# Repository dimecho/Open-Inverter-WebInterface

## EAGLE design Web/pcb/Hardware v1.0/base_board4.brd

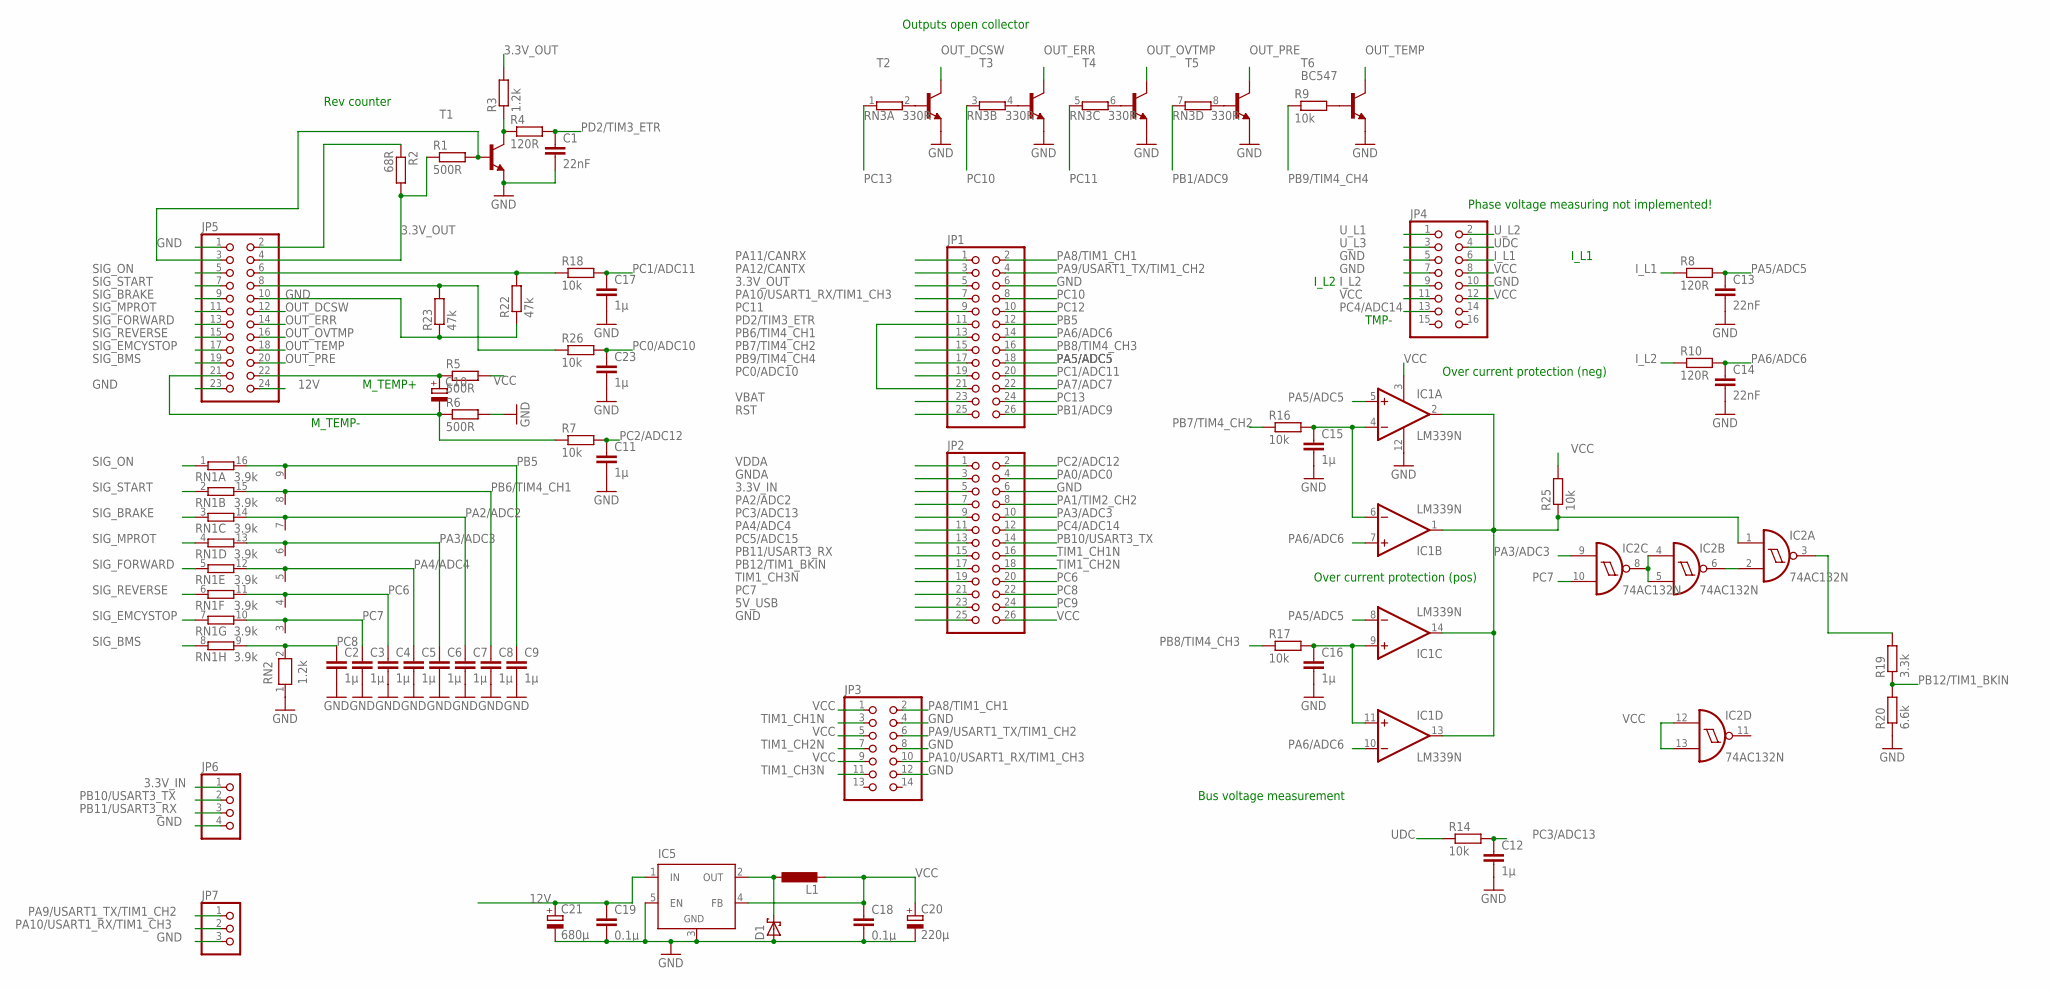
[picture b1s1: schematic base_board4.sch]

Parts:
C1, C13, C14: 22nF; C025-024X044
C2, C3, C4, C5, C6, C7, C8, C9, C11, C12, C15, C16, C17, C23: 1µ; C025-024X044
C10: CPOL-EUE2-4; E2-4
C18, C19: 0.1µ; C050-024X044
C20: 220µ; E2-4
C21: 680µ; E2,5-5
D1: SCHOTTKY-DIODEDO201T15; DO201T15
IC1: LM339N; DIL14
IC2: 74AC132N; DIL14
IC5: LM2596TV; TO220-51
JP1, JP2: PINHD-2X13; 2X13
JP3: PINHD-2X7; 2X07
JP4: PINHD-2X8; 2X08
JP5: PINHD-2X12; 2X12
JP6: PINHD-1X4; 1X04
JP7: PINHD-1X3; 1X03
L1: L-EUTJ3-U1; TJ3-U1
R1, R5, R6: 500R; 0207/10
R2: 68R; 0207/10
R3: 1.2k; 0207/10
R4, R8, R10: 120R; 0207/10
R7, R9, R14, R16, R17, R18, R25, R26: 10k; 0207/10
R19: 3.3k; 0207/10
R20: 6.6k; 0207/10
R22, R23: 47k; 0207/10
RN1: 3.9k; DIL16
RN2: 1.2k; RN-9
RN3: 330R; SIL8
T1: BC547B-NPN-TO92-EBC; TO92-EBC
T2, T3, T4, T5: -NPN-TO92-EBC; TO92-EBC
T6: BC547; TO92

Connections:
3.3V_IN: JP2.5, JP6.1
3.3V_OUT: JP1.5, JP5.4, R1.1, R2.2, R3.2
5V_USB: JP2.23
12V: C19.1, C21.+, IC5.1 (IN), JP5.24
GND: C1.2, C2.2, C3.2, C4.2, C5.2, C6.2, C7.2, C8.2, C9.2, C11.2, C12.2, C13.2, C14.2, C15.2, C16.2, C17.2, C18.2, C19.2, C20.-, C21.-, C23.2, D1.A, IC1.12 (GND), IC2.7 (GND), IC5.3 (GND), IC5.5 (EN), JP1.6, JP2.6, JP2.25, JP3.4, JP3.8, JP3.12, JP4.5, JP4.7, JP4.10, JP5.1, JP5.10, JP5.23, JP6.4, JP7.3, R6.2, R20.1, R22.1, R23.1, RN2.1, T1.E, T2.E, T3.E, T4.E, T5.E, T6.1 (E)
GNDA: JP2.3
I_L1: JP4.6, R8.1
I_L2: JP4.9, R10.1
N2: R3.1, R4.1, T1.C
unnamed: RN3.2, T2.B
unnamed: RN3.4 (2), T3.B
unnamed: JP5.2, R2.1
unnamed: RN3.6 (2), T4.B
unnamed: JP5.3, R1.2, T1.B
unnamed: RN3.8 (2), T5.B
unnamed: R9.2, T6.2 (B)
unnamed: IC2.3 (O), R19.2
unnamed: C16.1, IC1.9 (+IN), IC1.11 (+IN), R17.2
unnamed: IC2.2 (I1), IC2.6 (O)
unnamed: C10.+, JP5.22, R5.1
unnamed: D1.C, IC5.2 (OUT), L1.1
unnamed: C15.1, IC1.4 (-IN), IC1.6 (-IN), R16.2
unnamed: C10.-, JP5.21, R6.1, R7.1
unnamed: IC2.4 (I0), IC2.5 (I1), IC2.8 (O)
unnamed: IC1.1 (OUT), IC1.2 (OUT), IC1.13 (OUT), IC1.14 (OUT), IC2.1 (I0), R25.1
OUT_DCSW: JP5.12, T2.C
OUT_ERR: JP5.14, T3.C
OUT_OVTMP: JP5.16, T4.C
OUT_PRE: JP5.20, T5.C
OUT_TEMP: JP5.18, T6.3 (C)
PA0/ADC0: JP2.4
PA1/TIM2_CH2: JP2.8
PA2/ADC2: C7.1, JP2.7, RN1.14 (2), RN2.7
PA3/ADC3: C6.1, IC2.9 (I0), JP2.10, RN1.13 (2), RN2.6
PA4/ADC4: C5.1, JP2.11, RN1.12 (2), RN2.5
PA5/ADC5: C13.1, IC1.5 (+IN), IC1.8 (-IN), JP1.18, R8.2
PA6/ADC6: C14.1, IC1.7 (+IN), IC1.10 (-IN), JP1.14, R10.2
PA7/ADC7: JP1.22
PA8/TIM1_CH1: JP1.2, JP3.2
PA9/USART1_TX/TIM1_CH2: JP1.4, JP3.6, JP7.1
PA10/USART1_RX/TIM1_CH3: JP1.7, JP3.10, JP7.2
PA11/CANRX: JP1.1
PA12/CANTX: JP1.3
PB1/ADC9: JP1.26, RN3.7 (1)
PB5: C9.1, JP1.12, RN1.16 (2), RN2.9
PB6/TIM4_CH1: C8.1, JP1.13, RN1.15 (2), RN2.8
PB7/TIM4_CH2: JP1.15, R16.1
PB8/TIM4_CH3: JP1.16, R17.1
PB9/TIM4_CH4: JP1.17, R9.1
PB10/USART3_TX: JP2.14, JP6.2
PB11/USART3_RX: JP2.15, JP6.3
PB12/TIM1_BKIN: JP2.17, R19.1, R20.2
PC0/ADC10: C23.1, JP1.19, R26.2
PC1/ADC11: C17.1, JP1.20, R18.2
PC2/ADC12: C11.1, JP2.2, R7.2
PC3/ADC13: C12.1, JP2.9, R14.2
PC4/ADC14: JP2.12, JP4.13
PC5/ADC15: JP2.13
PC6: C4.1, JP2.20, RN1.11 (2), RN2.4
PC7: C3.1, IC2.10 (I1), JP2.21, RN1.10 (2), RN2.3
PC8: C2.1, JP2.22, RN1.9 (2), RN2.2
PC9: JP2.24
PC10: JP1.8, RN3.3 (1)
PC11: JP1.9, RN3.5 (1)
PC12: JP1.10
PC13: JP1.24, RN3.1
PD2/TIM3_ETR: C1.1, JP1.11, JP1.21, R4.2
RST: JP1.25
SIG_BMS: JP5.19, RN1.8 (1)
SIG_BRAKE: JP5.9, RN1.3 (1)
SIG_EMCYSTOP: JP5.17, RN1.7 (1)
SIG_FORWARD: JP5.13, RN1.5 (1)
SIG_MPROT: JP5.11, RN1.4 (1)
SIG_ON: JP5.5, RN1.1
SIG_REVERSE: JP5.15, RN1.6 (1)
SIG_START: JP5.7, RN1.2 (1)
TIM1_CH1N: JP2.16, JP3.3
TIM1_CH2N: JP2.18, JP3.7
TIM1_CH3N: JP2.19, JP3.11
UDC: JP4.4, R14.1
U_L1: JP4.1
U_L2: JP4.2
U_L3: JP4.3
VBAT: JP1.23
VCC: C18.1, C20.+, IC1.3 (V+), IC2.12 (I0), IC2.13 (I1), IC2.14 (VCC), IC5.4 (FB), JP2.26, JP3.1, JP3.5, JP3.9, JP4.8, JP4.11, JP4.12, L1.2, R5.2, R25.2
VDDA: JP2.1
X: JP5.6, R18.1, R22.2
Y: JP5.8, R23.2, R26.1

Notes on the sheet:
M_TEMP+
M_TEMP-
TMP-
Over current protection (pos)
Outputs open collector
Phase voltage measuring not implemented!
Bus voltage measurement
Rev counter
Over current protection (neg)
I_L1
I_L2

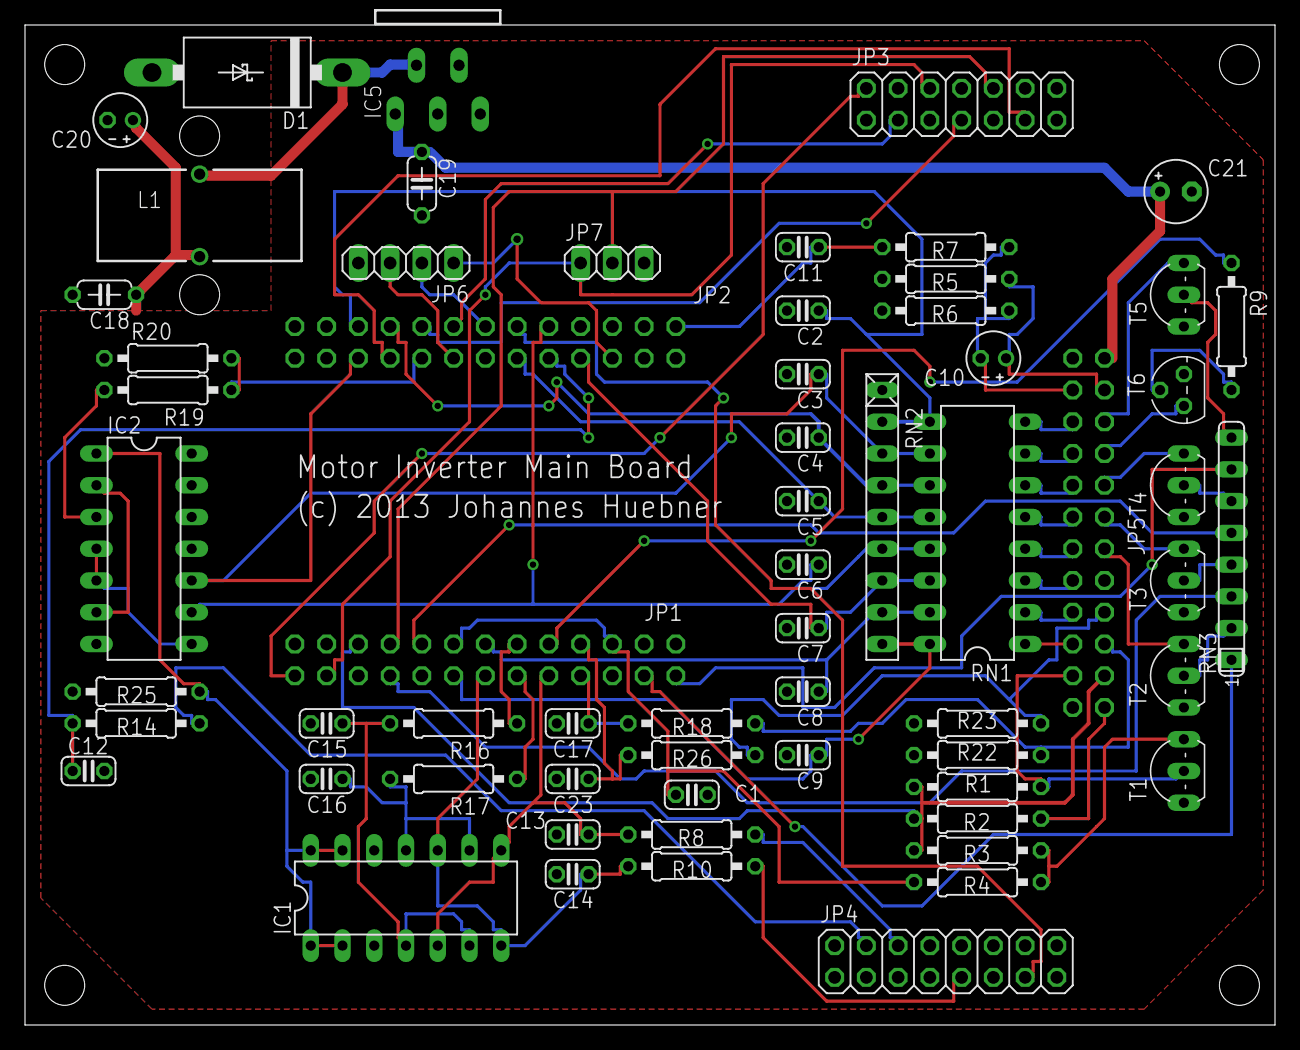
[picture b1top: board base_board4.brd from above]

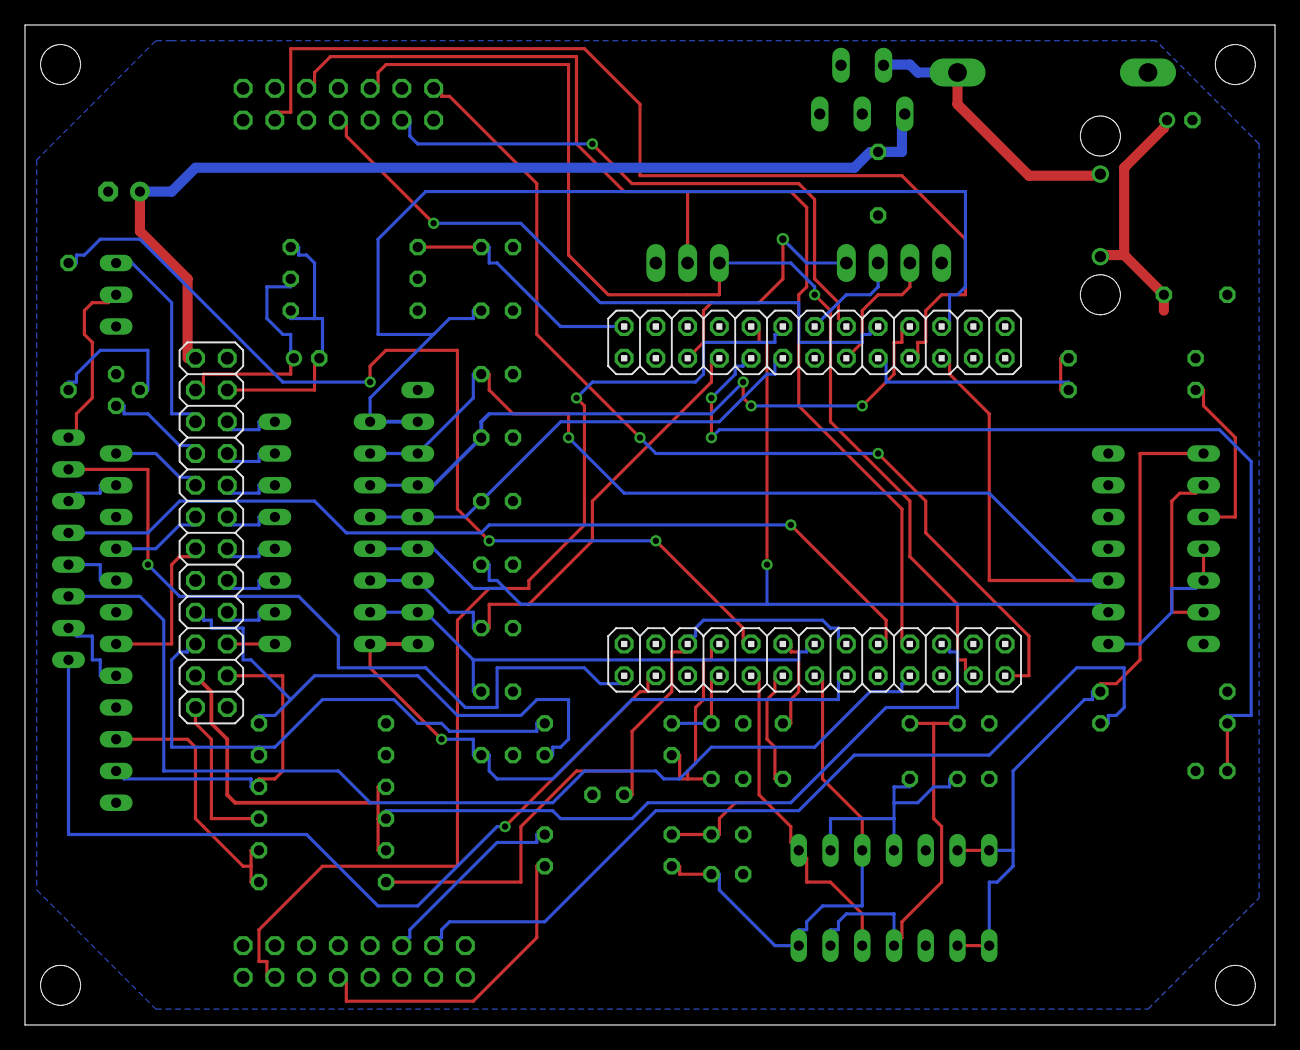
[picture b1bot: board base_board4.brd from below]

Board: 2 copper layers, 100.0 x 80.0 mm, 63 parts (3 on the bottom side), 72 nets.

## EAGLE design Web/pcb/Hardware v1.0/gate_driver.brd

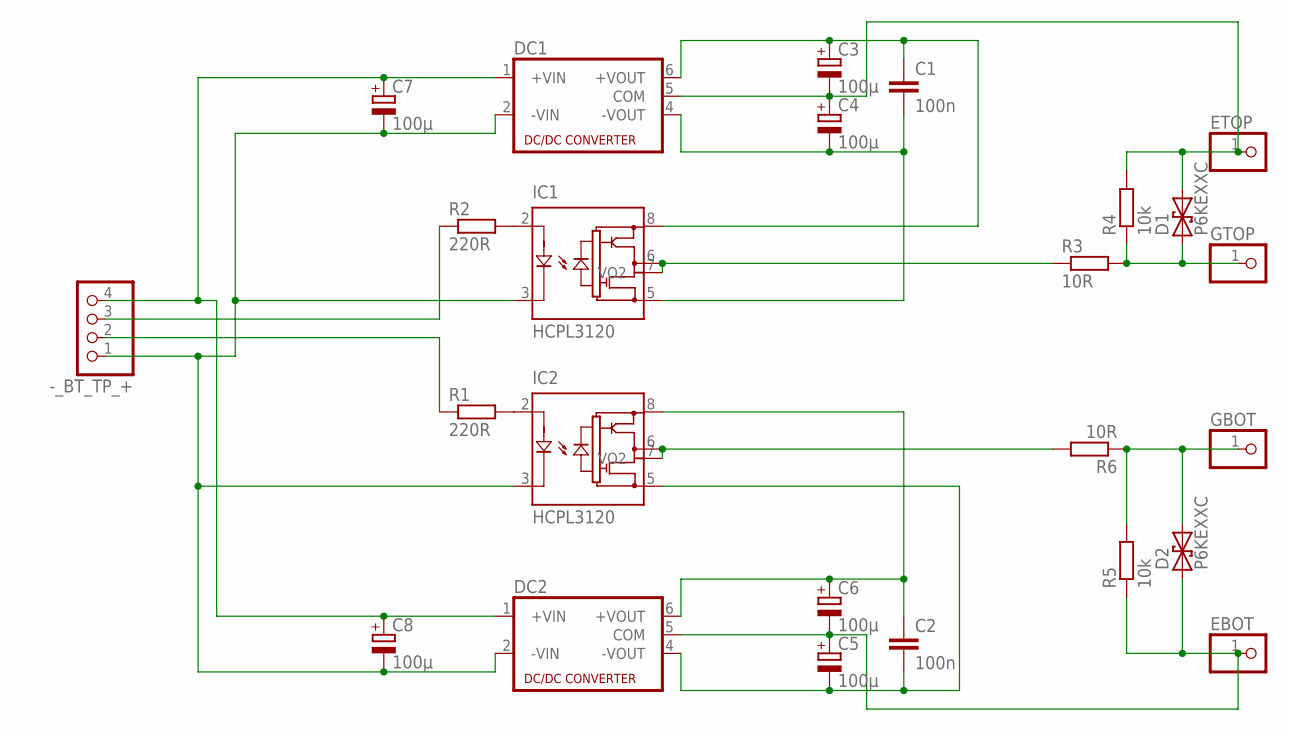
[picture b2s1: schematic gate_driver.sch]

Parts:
-_BT_TP_+: PINHD-1X4; 1X04
C1, C2: 100n; C050-025X075
C3, C4, C5, C6: 100µ; E2,5-6E
C7, C8: 100µ; E2,5-5
D1, D2: P6KEXXC; CB417-15
DC1, DC2: NMA
EBOT: PINHD-1X1; 1X01
ETOP: PINHD-1X1; 1X01
GBOT: PINHD-1X1; 1X01
GTOP: PINHD-1X1; 1X01
IC1, IC2: HCPL3120; DIL08
R1, R2: 220R; 0207/10
R3, R6: 10R; 0309/12
R4, R5: 10k; 0207/10

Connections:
EBOT: C5.+, C6.-, D2.A (1), DC2.5 (COM), EBOT.1, R5.1
ETOP: C3.-, C4.+, D1.C (2), DC1.5 (COM), ETOP.1, R4.2
GBOT: D2.C (2), GBOT.1, R5.2, R6.1
GND: -_BT_TP_+.1, C7.-, C8.-, DC1.2 (-VIN), DC2.2 (-VIN), IC1.3 (CATHODE), IC2.3 (CATHODE)
GTOP: D1.A (1), GTOP.1, R3.2, R4.1
unnamed: IC2.2 (ANODE), R1.2
unnamed: IC1.2 (ANODE), R2.2
unnamed: C1.2, C4.-, DC1.4 (-VOUT), IC1.5 (VEE)
unnamed: C1.1, C3.+, DC1.6 (+VOUT), IC1.8 (VCC)
unnamed: C2.1, C6.+, DC2.6 (+VOUT), IC2.8 (VCC)
unnamed: C2.2, C5.-, DC2.4 (-VOUT), IC2.5 (VEE)
unnamed: IC1.6 (VO), IC1.7 (VO2), R3.1
unnamed: IC2.6 (VO), IC2.7 (VO2), R6.2
unnamed: -_BT_TP_+.4, C7.+, C8.+, DC1.1 (+VIN), DC2.1 (+VIN)
unnamed: -_BT_TP_+.3, R2.1
unnamed: -_BT_TP_+.2, R1.1

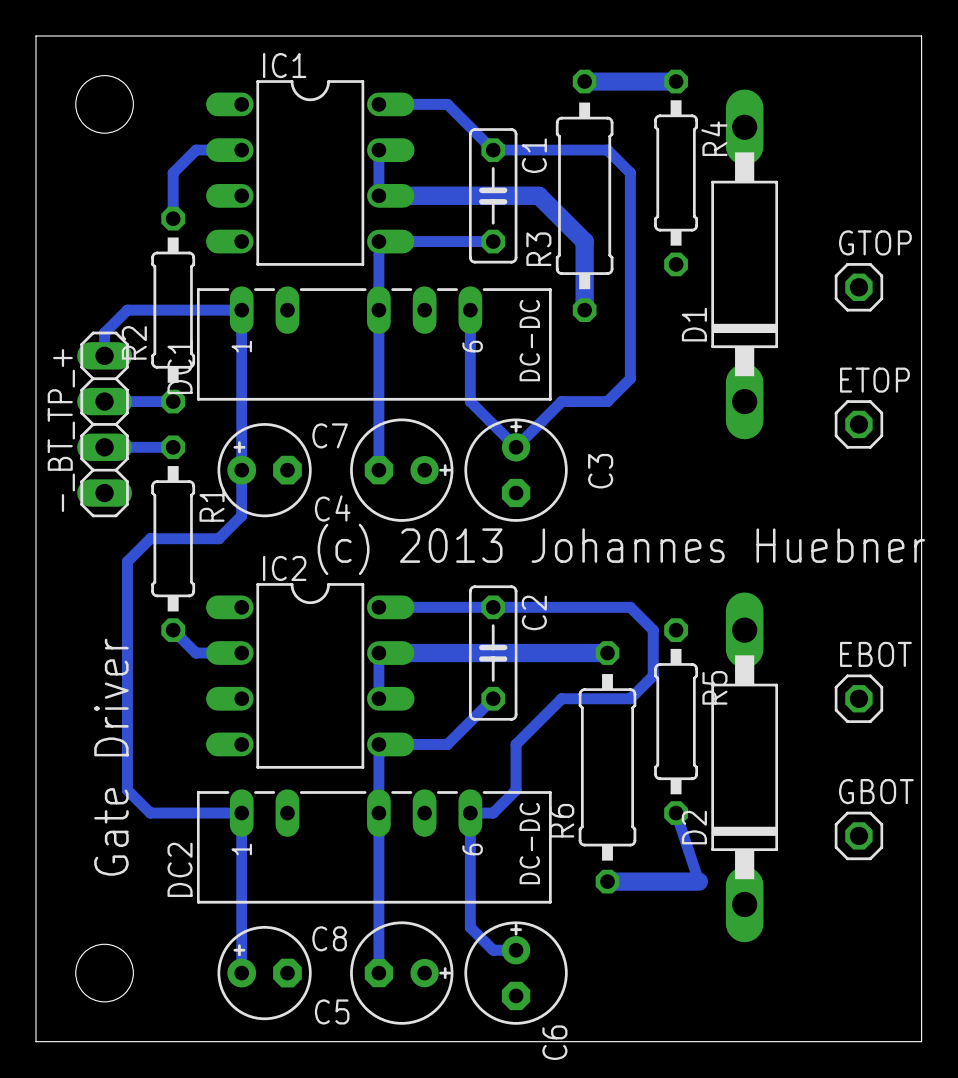
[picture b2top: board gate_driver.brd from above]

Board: 2 copper layers, 49.2 x 55.9 mm, 25 parts (0 on the bottom side), 16 nets.

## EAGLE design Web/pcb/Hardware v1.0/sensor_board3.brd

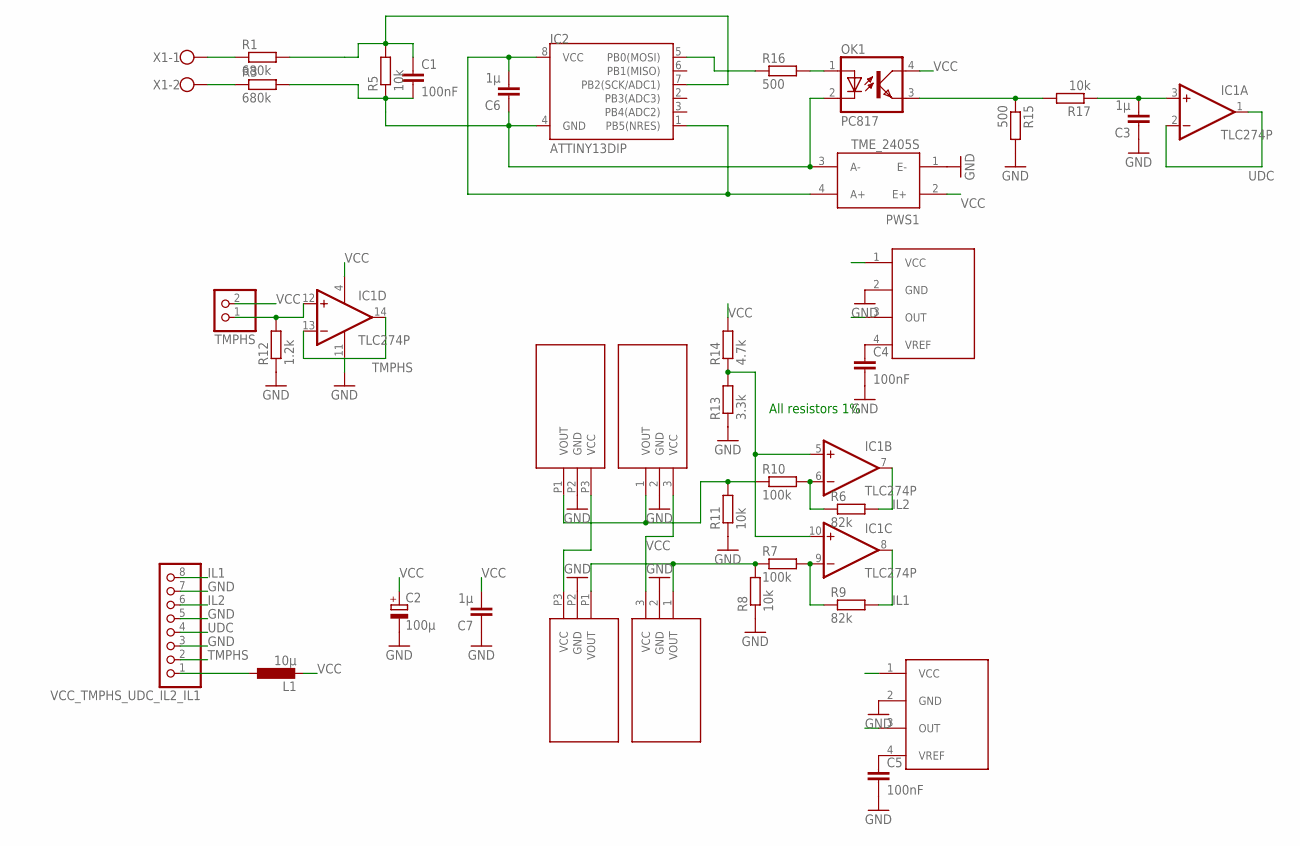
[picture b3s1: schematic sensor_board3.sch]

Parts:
C1, C4, C5: 100nF; C025-024X044
C2: 100µ; E2,5-6E
C3, C6, C7: 1µ; C025-024X044
IC1: TLC274P; DIL14
IC2: ATTINY13DIP; DIP08
L1: 10µ; 0207/12
OK1: PC817; DIL04
PWS1: TME_2405S; TMEXXXXS
R1, R3: 680k; 0207/10
R5, R8, R11, R17: 10k; 0207/10
R6, R9: 82k; 0207/10
R7, R10: 100k; 0207/10
R12: 1.2k; 0207/10
R13: 3.3k; 0207/10
R14: 4.7k; 0207/10
R15, R16: 500; 0207/10
TMPHS: PINHD-1X2; 1X02
U$1, U$2: TAMURA_L01Z_S05
U$3, U$4: HTFS
U$5, U$6: TAMURA_L06P_S05L06P; TAMURA_L06P_S05
VCC_TMPHS_UDC_IL2_IL1: PINHD-1X8; 1X08
X1: W237-102

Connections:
GND: C2.-, C3.1, C4.2, C5.2, C7.1, IC1.11 (V-), PWS1.1 (E-), R8.1, R11.1, R12.1, R13.1, R15.2, U$1.2 (GND), U$2.2 (GND), U$3.2 (GND), U$4.2 (GND), U$5.P2 (GND), U$6.P2 (GND), VCC_TMPHS_UDC_IL2_IL1.3, VCC_TMPHS_UDC_IL2_IL1.5, VCC_TMPHS_UDC_IL2_IL1.7
GND2: C1.2, C6.1, IC2.4 (GND), OK1.2 (C), PWS1.3 (A-), R3.2, R5.1
IL1: IC1.8 (OUT), R9.2, VCC_TMPHS_UDC_IL2_IL1.8
IL2: IC1.7 (OUT), R6.2, VCC_TMPHS_UDC_IL2_IL1.6
unnamed: IC1.5 (+IN), IC1.10 (+IN), R13.2, R14.1
unnamed: C1.1, IC2.7 (PB2(SCK/ADC1)), R1.2, R5.2
unnamed: R1.1, X1.1
unnamed: R3.1, X1.2
unnamed: L1.1, VCC_TMPHS_UDC_IL2_IL1.1
unnamed: IC1.9 (-IN), R7.2, R9.1
unnamed: IC1.6 (-IN), R6.1, R10.2
unnamed: OK1.3 (EMIT), R15.1, R17.2
unnamed: C4.1, U$3.4 (VREF)
unnamed: C5.1, U$4.4 (VREF)
unnamed: IC1.12 (+IN), R12.2, TMPHS.1
unnamed: OK1.1 (A), R16.2
unnamed: IC2.5 (PB0(MOSI)), R16.1
unnamed: C3.2, IC1.3 (+IN), R17.1
TMPHS: IC1.13 (-IN), IC1.14 (OUT), VCC_TMPHS_UDC_IL2_IL1.2
UDC: IC1.1 (OUT), IC1.2 (-IN), VCC_TMPHS_UDC_IL2_IL1.4
VCC: C2.+, C7.2, IC1.4 (V+), L1.2, OK1.4 (COL), PWS1.2 (E+), R14.2, TMPHS.2, U$1.3 (VCC), U$2.3 (VCC), U$3.1 (VCC), U$4.1 (VCC), U$5.P3 (VCC), U$6.P3 (VCC)
VCC2: C6.2, IC2.1 (PB5(NRES)), IC2.8 (VCC), PWS1.4 (A+)
VOUT1: R7.1, R8.2, U$2.1 (VOUT), U$4.3 (OUT), U$6.P1 (VOUT)
VOUT2: R10.1, R11.2, U$1.1 (VOUT), U$3.3 (OUT), U$5.P1 (VOUT)

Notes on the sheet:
All resistors 1%

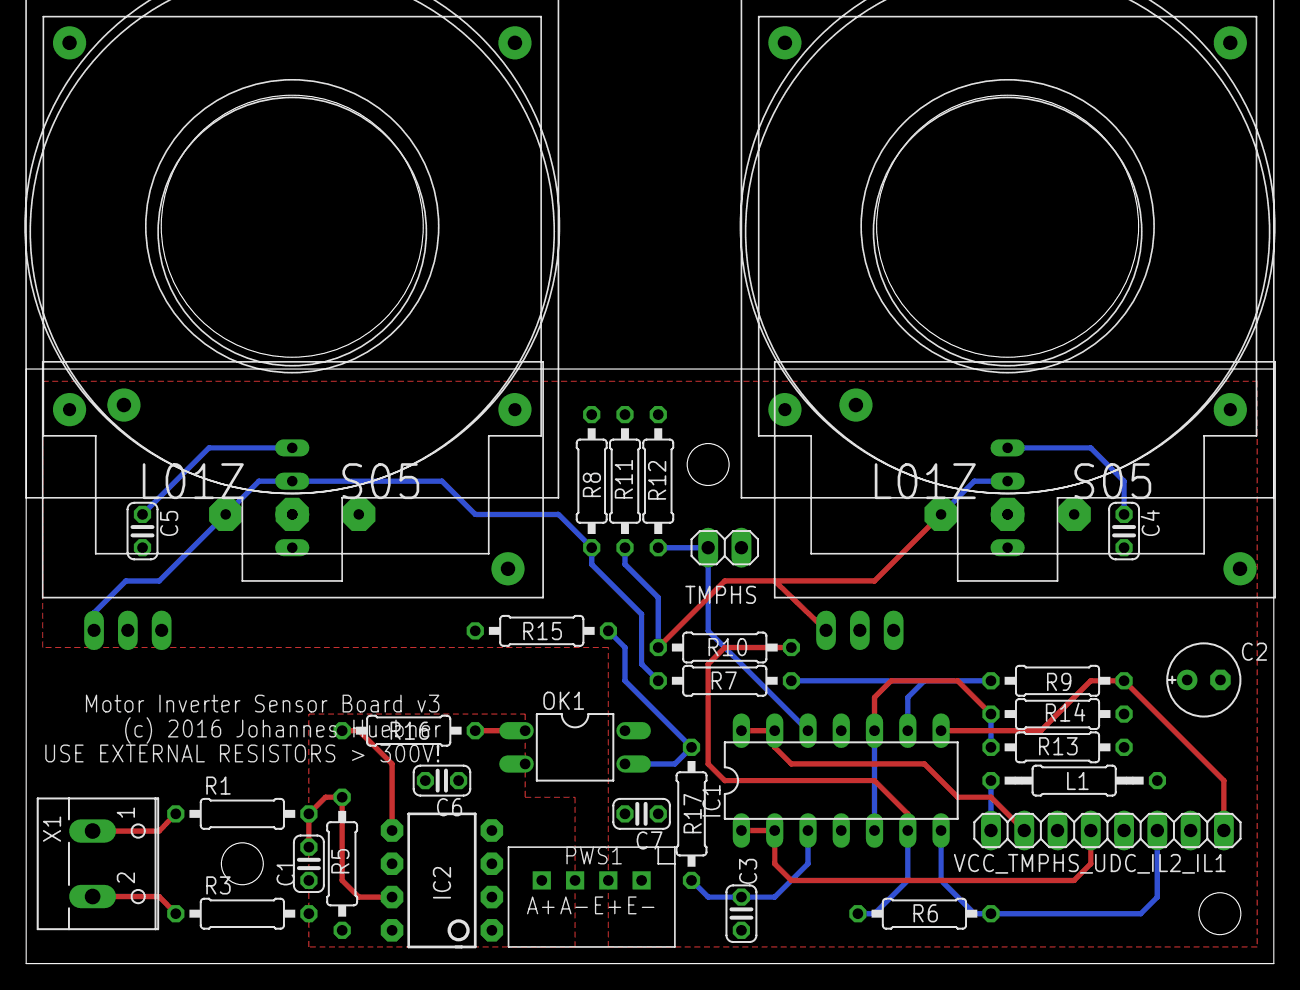
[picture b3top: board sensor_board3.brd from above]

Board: 2 copper layers, 95.2 x 45.4 mm, 36 parts (0 on the bottom side), 24 nets.

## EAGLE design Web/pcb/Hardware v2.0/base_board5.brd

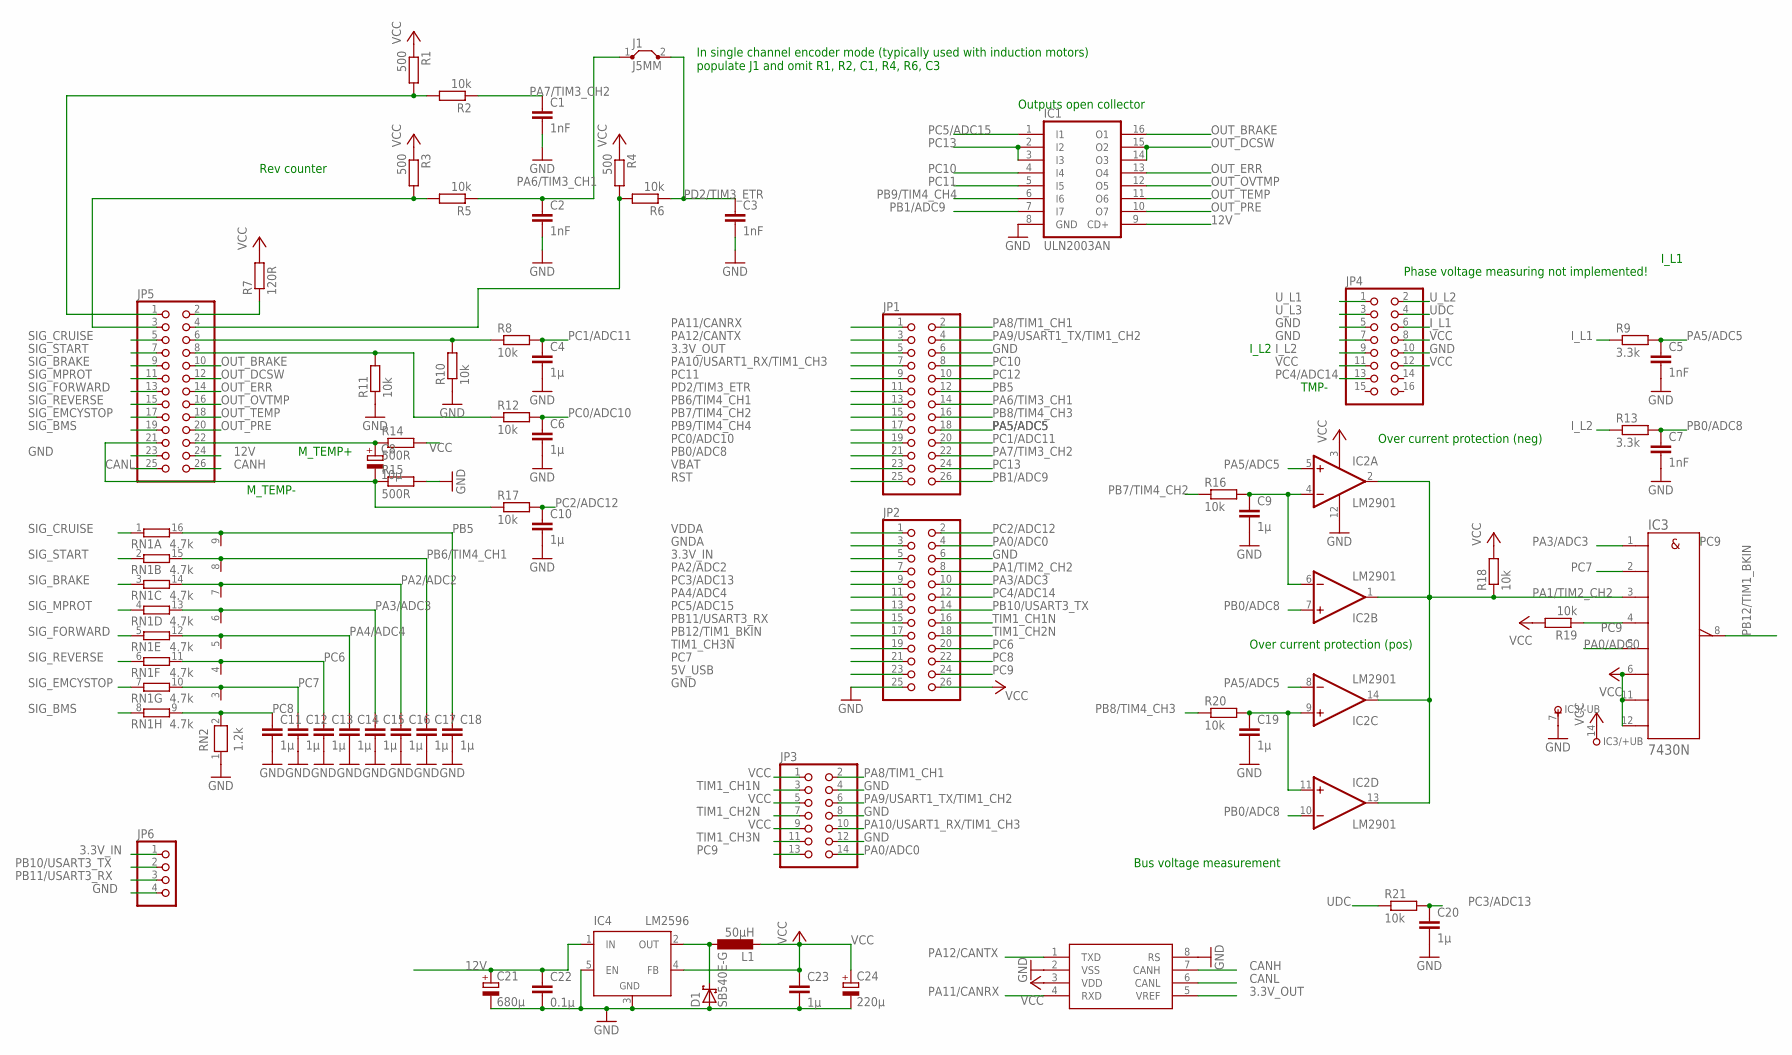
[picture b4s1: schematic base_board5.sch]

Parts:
C1, C2, C3, C5, C7: 1nF; C025-024X044
C4, C6, C9, C10, C11, C12, C13, C14, C15, C16, C17, C18, C19, C20, C23: 1µ; C025-024X044
C8: 10µ; E2-4
C21: 680µ; E2,5-5
C22: 0.1µ; C050-024X044
C24: 220µ; E2-4
D1: SB540E-G; DO201T15
IC1: ULN2003AN; DIL16
IC2: LM2901; DIL14
IC3: 7430N; DIL14
IC4: LM2596; TO220-51
IC5: MCP2562P; DIL08
J1: J5MM; 05
JP1, JP2, JP5: PINHD-2X13; 2X13
JP3: PINHD-2X7; 2X07
JP4: PINHD-2X8; 2X08
JP6: PINHD-1X4; 1X04
L1: 50µH; TJ3-U1
R1, R3, R4: 500; 0207/10
R2, R5, R6, R8, R10, R11, R12, R16, R17, R18, R19, R20, R21: 10k; 0207/10
R7: 120R; 0207/10
R9, R13: 3.3k; 0207/10
R14, R15: 500R; 0207/10
RN1: 4.7k; DIL16
RN2: 1.2k; RN-9

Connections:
3.3V_IN: JP2.5, JP6.1
3.3V_OUT: IC5.5 (VREF), JP1.5
5V_USB: JP2.23
12V: C21.+, C22.1, IC1.9 (CD+), IC4.1 (IN), JP5.24
CANH: IC5.7 (CANH), JP5.26
CANL: IC5.6 (CANL), JP5.25
GND: C1.2, C2.2, C3.2, C4.2, C5.2, C6.2, C7.2, C9.2, C10.2, C11.2, C12.2, C13.2, C14.2, C15.2, C16.2, C17.2, C18.2, C19.2, C20.2, C21.-, C22.2, C23.2, C24.-, D1.A, IC1.8 (GND), IC2.12 (GND), IC3.7 (-UB), IC4.3 (GND), IC4.5 (EN), IC5.2 (VSS), IC5.8 (RS), JP1.6, JP2.6, JP2.25, JP3.4, JP3.8, JP3.12, JP4.5, JP4.7, JP4.10, JP5.23, JP6.4, R10.1, R11.1, R15.2, RN2.1
GNDA: JP2.3
I_L1: JP4.6, R9.1
I_L2: JP4.9, R13.1
unnamed: JP5.2, R7.1
unnamed: JP5.3, R3.2, R5.2
unnamed: JP5.1, R1.2, R2.2
unnamed: C19.1, IC2.9 (+IN), IC2.11 (+IN), R20.2
unnamed: JP5.4, R4.2, R6.2
unnamed: C8.+, JP5.22, R14.1
unnamed: D1.C, IC4.2 (OUT), L1.1
unnamed: C9.1, IC2.4 (-IN), IC2.6 (-IN), R16.2
unnamed: C8.-, JP5.21, R15.1, R17.1
OUT_BRAKE: IC1.16 (O1), JP5.10
OUT_DCSW: IC1.14 (O3), IC1.15 (O2), JP5.12
OUT_ERR: IC1.13 (O4), JP5.14
OUT_OVTMP: IC1.12 (O5), JP5.16
OUT_PRE: IC1.10 (O7), JP5.20
OUT_TEMP: IC1.11 (O6), JP5.18
PA0/ADC0: IC3.5 (E), JP2.4, JP3.14
PA1/TIM2_CH2: IC2.1 (OUT), IC2.2 (OUT), IC2.13 (OUT), IC2.14 (OUT), IC3.3 (C), JP2.8, R18.1
PA2/ADC2: C16.1, JP2.7, RN1.14 (2), RN2.7
PA3/ADC3: C15.1, IC3.1 (A), JP2.10, RN1.13 (2), RN2.6
PA4/ADC4: C14.1, JP2.11, RN1.12 (2), RN2.5
PA5/ADC5: C5.1, IC2.5 (+IN), IC2.8 (-IN), JP1.18, R9.2
PA6/TIM3_CH1: C2.1, J1.1, JP1.14, R5.1
PA7/TIM3_CH2: C1.1, JP1.22, R2.1
PA8/TIM1_CH1: JP1.2, JP3.2
PA9/USART1_TX/TIM1_CH2: JP1.4, JP3.6
PA10/USART1_RX/TIM1_CH3: JP1.7, JP3.10
PA11/CANRX: IC5.4 (RXD), JP1.1
PA12/CANTX: IC5.1 (TXD), JP1.3
PB0/ADC8: C7.1, IC2.7 (+IN), IC2.10 (-IN), JP1.21, R13.2
PB1/ADC9: IC1.7 (I7), JP1.26
PB5: C18.1, JP1.12, RN1.16 (2), RN2.9
PB6/TIM4_CH1: C17.1, JP1.13, RN1.15 (2), RN2.8
PB7/TIM4_CH2: JP1.15, R16.1
PB8/TIM4_CH3: JP1.16, R20.1
PB9/TIM4_CH4: IC1.6 (I6), JP1.17
PB10/USART3_TX: JP2.14, JP6.2
PB11/USART3_RX: JP2.15, JP6.3
PB12/TIM1_BKIN: IC3.8 (Y), JP2.17
PC0/ADC10: C6.1, JP1.19, R12.2
PC1/ADC11: C4.1, JP1.20, R8.2
PC2/ADC12: C10.1, JP2.2, R17.2
PC3/ADC13: C20.1, JP2.9, R21.2
PC4/ADC14: JP2.12, JP4.13
PC5/ADC15: IC1.1 (I1), JP2.13
PC6: C13.1, JP2.20, RN1.11 (2), RN2.4
PC7: C12.1, IC3.2 (B), JP2.21, RN1.10 (2), RN2.3
PC8: C11.1, JP2.22, RN1.9 (2), RN2.2
PC9: IC3.4 (D), JP2.24, JP3.13, R19.1
PC10: IC1.4 (I4), JP1.8
PC11: IC1.5 (I5), JP1.9
PC12: JP1.10
PC13: IC1.2 (I2), IC1.3 (I3), JP1.24
PD2/TIM3_ETR: C3.1, J1.2, JP1.11, R6.1
RST: JP1.25
SIG_BMS: JP5.19, RN1.8 (1)
SIG_BRAKE: JP5.9, RN1.3 (1)
SIG_CRUISE: JP5.5, RN1.1
SIG_EMCYSTOP: JP5.17, RN1.7 (1)
SIG_FORWARD: JP5.13, RN1.5 (1)
SIG_MPROT: JP5.11, RN1.4 (1)
SIG_REVERSE: JP5.15, RN1.6 (1)
SIG_START: JP5.7, RN1.2 (1)
TIM1_CH1N: JP2.16, JP3.3
TIM1_CH2N: JP2.18, JP3.7
TIM1_CH3N: JP2.19, JP3.11
UDC: JP4.4, R21.1
U_L1: JP4.1
U_L2: JP4.2
U_L3: JP4.3
VBAT: JP1.23
VCC: C23.1, C24.+, IC2.3 (V+), IC3.6 (F), IC3.11 (G), IC3.12 (H), IC3.14 (+UB), IC4.4 (FB), IC5.3 (VDD), JP2.26, JP3.1, JP3.5, JP3.9, JP4.8, JP4.11, JP4.12, L1.2, R1.1, R3.1, R4.1, R7.2, R14.2, R18.2, R19.2
VDDA: JP2.1
X: JP5.6, R8.1, R10.2
Y: JP5.8, R11.2, R12.1

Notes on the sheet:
M_TEMP+
M_TEMP-
TMP-
Over current protection (pos)
Outputs open collector
Phase voltage measuring not implemented!
Bus voltage measurement
Rev counter
Over current protection (neg)
I_L1
I_L2
In single channel encoder mode (typically used with induction motors) populate J1 and omit R1, R2, C1, R4, R6, C3

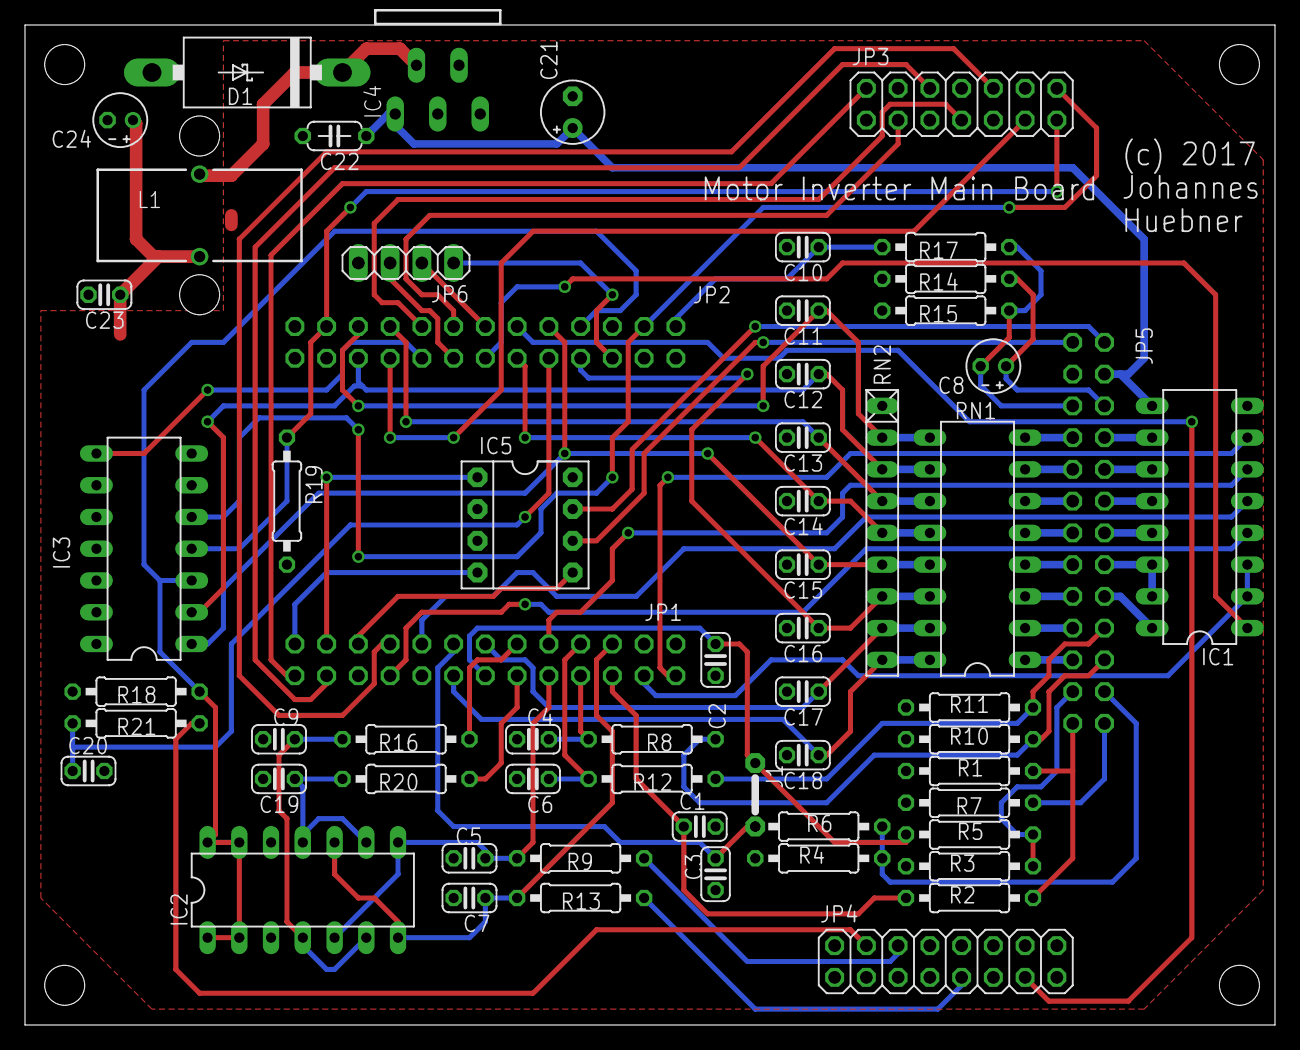
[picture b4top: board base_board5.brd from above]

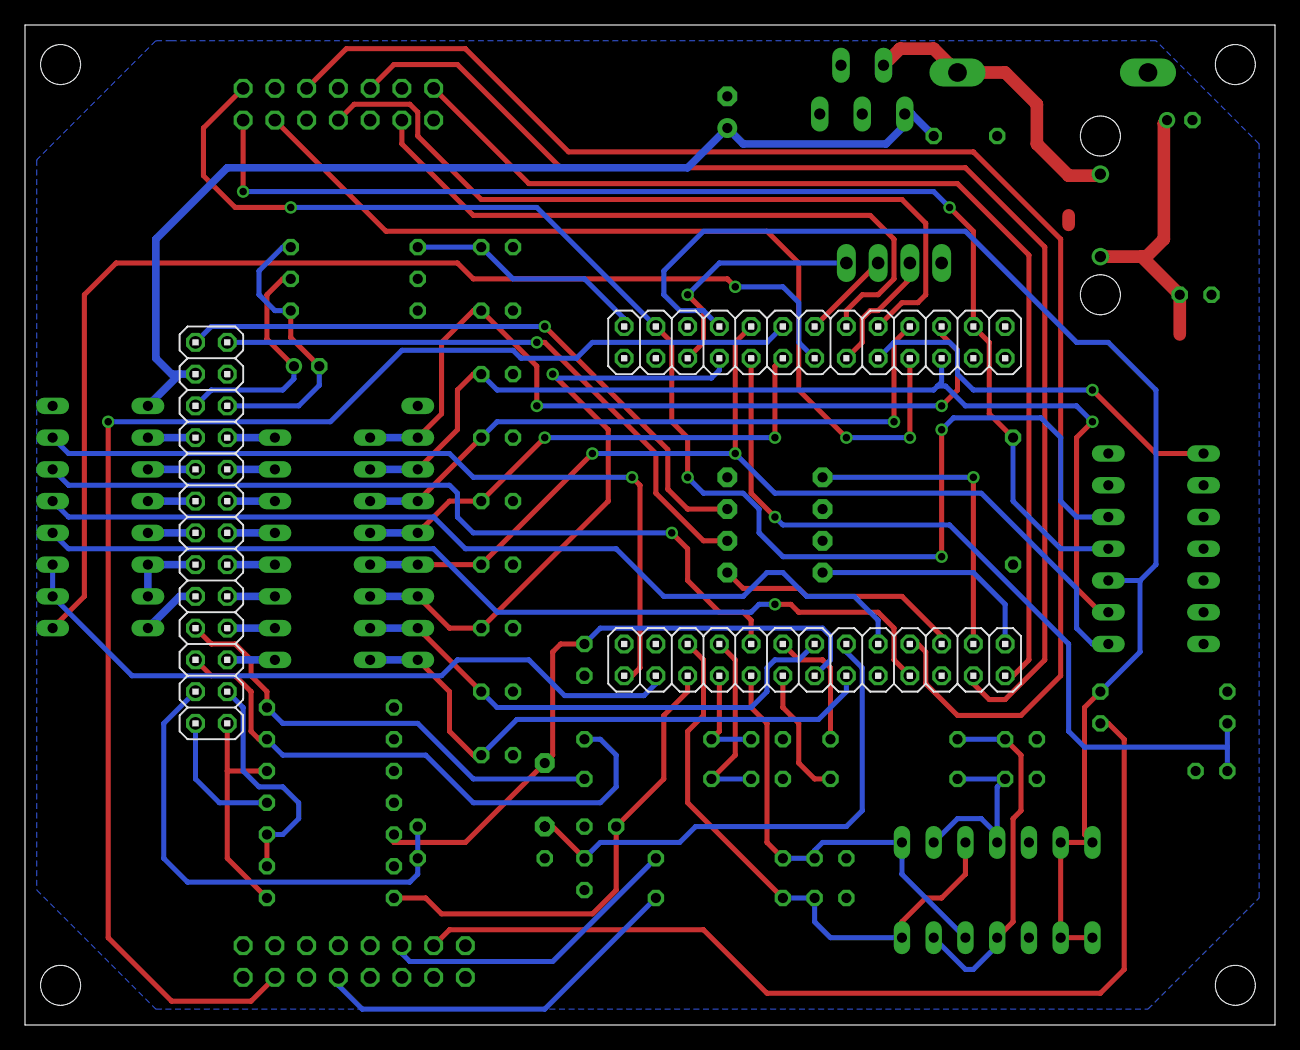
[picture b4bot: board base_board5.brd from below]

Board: 2 copper layers, 100.0 x 80.0 mm, 61 parts (3 on the bottom side), 75 nets.

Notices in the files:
Web/pcb/Hardware v1.0/base_board4.brd:
(c) 2013 Johannes Huebner
Web/pcb/Hardware v1.0/sensor_board3.brd:
(c) 2016 Johannes Huebner
Web/pcb/Hardware v2.0/base_board5.brd:
(c) 2017
parts and their libraries:
SparkFun-DigitalIC: Licensing: CC v3.0 Share-Alike You are welcome to use this library for commercial purposes.
